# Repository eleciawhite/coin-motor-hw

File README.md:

coin-motor-hw (Motor Driver Passthrough)
=============
This repository carries the information for fabricating a board that can drive 
a motor with a MOSFET (and pass through other signals)

Some expository and description can be found here: 
http://www.logicalelegance.com/journey/2014/03/releasing-boards/

The original schematic can be found via DigiKey's SchemeIt (which does not 
have layout capabilities at this time):
http://www.digikey.com/schemeit/#fba

The layout was done by Casey Kikendall. (Thank you!)

Pin out:
1 - motor signal
2 - ground
3 - power
4 - passA (I2C SDA)
5 - passB (I2C SCL)

With the N-Channel MOSFET specified in the BOM, a 5V motor can draw a constant 
~270mA (@25C, 210mA @70C). Pulsing the FET or using a higher voltage can lead 
to higher current throughput.

While the MOSFET can pass 60V on the drain side, it turns on at 2V on the 
gate side. (It can go to 20V on the gate side, though I'm driving it with a 
3.3V low current source GPIO.)

This board was designed to work with a 2.7-3.3 V coin-cell style motor (see 
BOM for link to datasheet). This motor has a start up current of 120mA (max) 
and 90mA normal. A more powerful motor could be used with this board.

The pass through signals are (for my project) used for I2C communication to 
a series of accelerometers. However, the are any signals you want to pass 
through.

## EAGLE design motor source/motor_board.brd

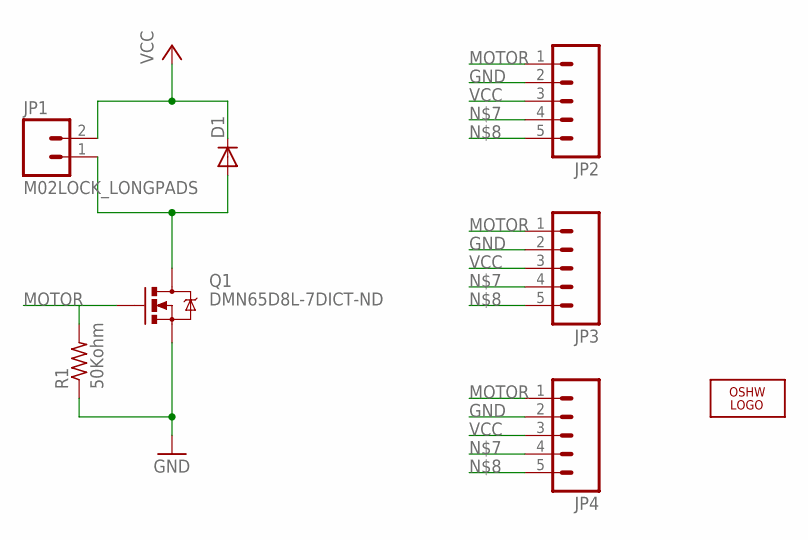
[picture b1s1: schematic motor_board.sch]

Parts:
D1: DIODE-DO214AA; DO214AA
JP1: M02LOCK_LONGPADS; 1X02_LOCK_LONGPADS
JP2, JP3, JP4: M05PTH; 1X05
LOGO2: OSHW_LOGO_6MILX0100-NT; OSHW_6X100_NOTEXT
Q1: DMN65D8L-7DICT-ND; SOT23
R1: 50Kohm; M1206

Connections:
GND: JP2.2, JP3.2, JP4.2, Q1.2 (S), R1.1
MOTOR: JP2.1, JP3.1, JP4.1, Q1.1 (G), R1.2
unnamed: D1.A, JP1.1, Q1.3 (D)
unnamed: JP2.4, JP3.4, JP4.4
unnamed: JP2.5, JP3.5, JP4.5
VCC: D1.C, JP1.2, JP2.3, JP3.3, JP4.3

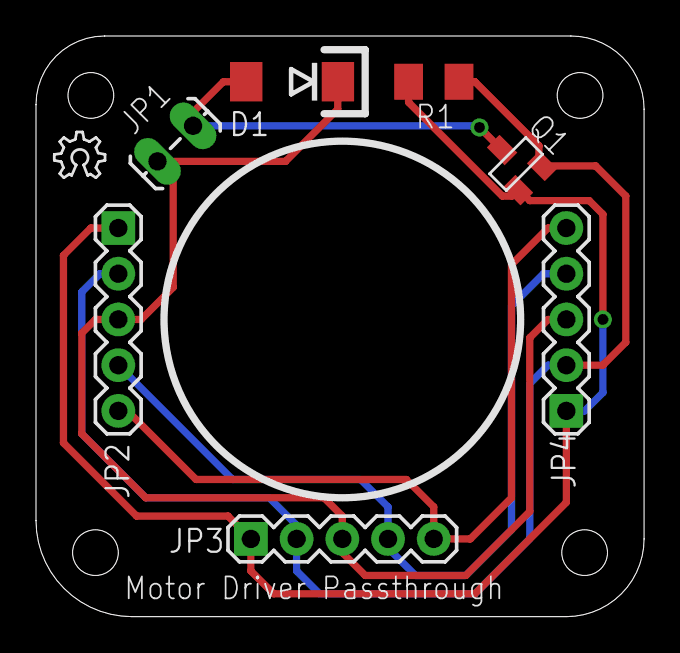
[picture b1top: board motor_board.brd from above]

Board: 2 copper layers, 33.8 x 32.3 mm, 8 parts (0 on the bottom side), 6 nets.

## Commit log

2014-03-17 Source files from Casey plus BOM from Digikey order and update of the readme.
2014-03-17 Updating readme.
2014-05-13 Updated readme to give specs and pinout (and all the stuff I keep having to look up)

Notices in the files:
parts and their libraries:
SparkFun-DiscreteSemi: Licensing: CC v3.0 Share-Alike You are welcome to use this library for commercial purposes.
